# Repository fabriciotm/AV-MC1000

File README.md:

# AV_MC1000
Saída AV para o CCE MC1000.

Projeto original do Victor Trucco disponível em http://www.victortrucco.com/Diversos/MC1000/MC1000

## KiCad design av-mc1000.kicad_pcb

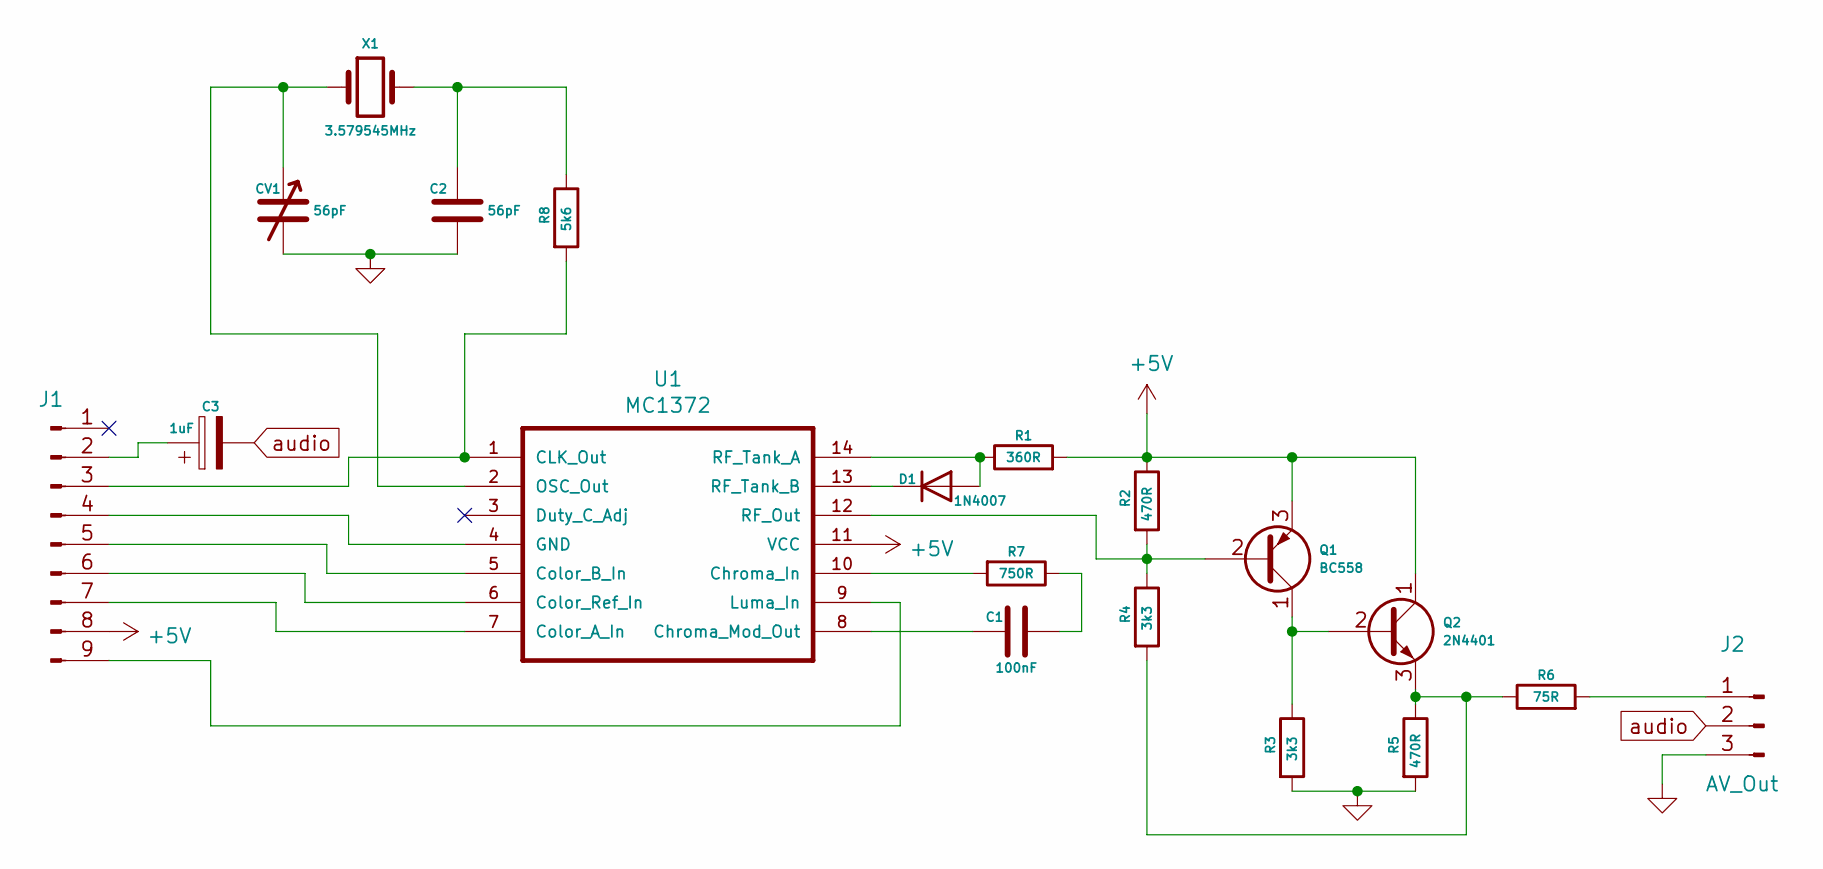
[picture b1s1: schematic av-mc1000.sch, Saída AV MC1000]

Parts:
C1: 100nF; C_Disc_D5.0mm_W2.5mm_P5.00mm
C2: 56pF; C_Disc_D5.0mm_W2.5mm_P5.00mm
C3: 1uF; CP_Radial_D5.0mm_P2.50mm
CV1: 56pF; trimmer
D1: 1N4007; D_DO-41_SOD81_P7.62mm_Horizontal
J1: Conn_01x09_Male; PinHeader_1x09_P2.54mm_Vertical
J2: AV_Out; PinHeader_1x03_P2.54mm_Vertical
Q1: BC558; TO-92_Inline
Q2: 2N4401; TO-92_Inline
R1: 360R; R_Axial_DIN0207_L6.3mm_D2.5mm_P7.62mm_Horizontal
R2, R5: 470R; R_Axial_DIN0207_L6.3mm_D2.5mm_P7.62mm_Horizontal
R3, R4: 3k3; R_Axial_DIN0207_L6.3mm_D2.5mm_P7.62mm_Horizontal
R6: 75R; R_Axial_DIN0207_L6.3mm_D2.5mm_P7.62mm_Horizontal
R7: 750R; R_Axial_DIN0207_L6.3mm_D2.5mm_P7.62mm_Horizontal
R8: 5k6; R_Axial_DIN0207_L6.3mm_D2.5mm_P7.62mm_Horizontal
U1: MC1372; DIP-14_W7.62mm
X1: 3.579545MHz; Crystal_HC49-4H_Vertical

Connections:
+5V: J1.8, Q1.3 (E), Q2.1 (C), R1.2, R2.1, U1.11 (VCC)
unnamed: C1.1, U1.8 (Chroma_Mod_Out)
unnamed: C1.2, R7.1
unnamed: C2.2, R8.1, X1.2
unnamed: C3.1, J1.2
unnamed: CV1.1, U1.2 (OSC_Out), X1.1
unnamed: D1.1 (K), U1.13 (RF_Tank_B)
unnamed: D1.2 (A), R1.1, U1.14 (RF_Tank_A)
unnamed: J1.3, R8.2, U1.1 (CLK_Out)
unnamed: J1.5, U1.5 (Color_B_In)
unnamed: J1.6, U1.6 (Color_Ref_In)
unnamed: J1.7, U1.7 (Color_A_In)
unnamed: J1.9, U1.9 (Luma_In)
unnamed: J2.1, R6.2
unnamed: Q1.1 (C), Q2.2 (B), R3.1
unnamed: Q1.2 (B), R2.2, R4.1, U1.12 (RF_Out)
unnamed: Q2.3 (E), R4.2, R5.1, R6.1
unnamed: R7.2, U1.10 (Chroma_In)
audio: C3.2, J2.2

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
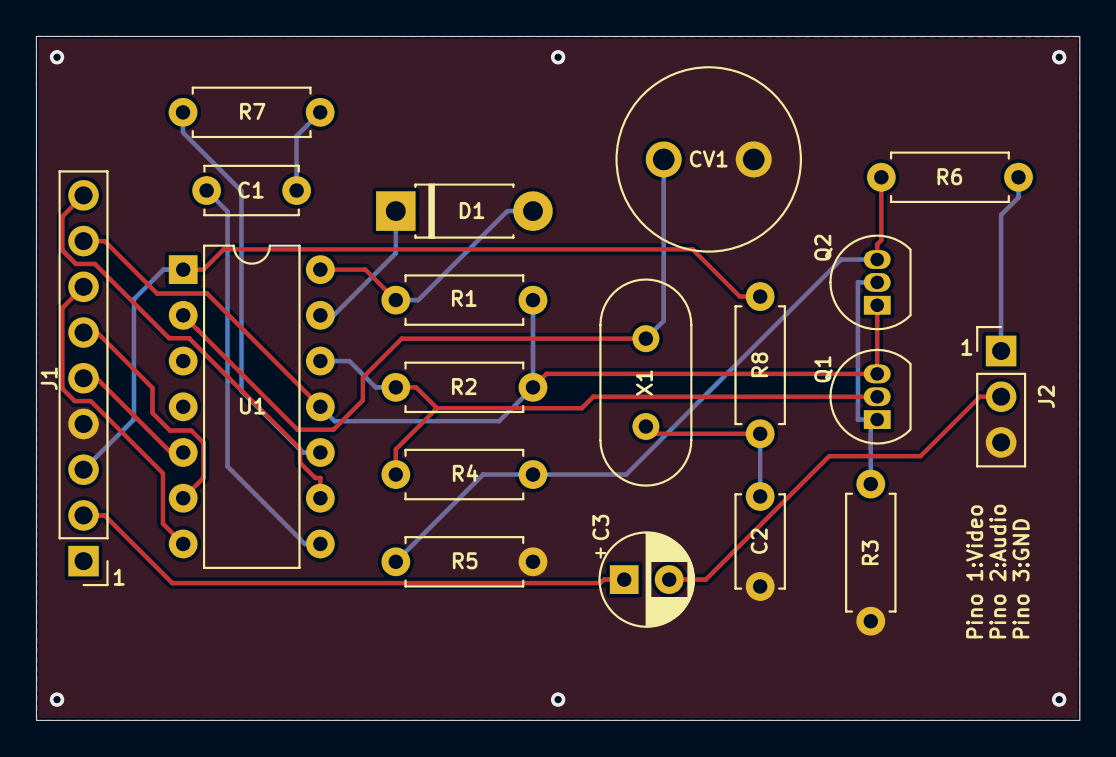
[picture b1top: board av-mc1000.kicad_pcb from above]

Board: 2 copper layers, 58.0 x 38.0 mm, 19 parts (0 on the bottom side), 20 nets.

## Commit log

2020-08-07 Create teste
